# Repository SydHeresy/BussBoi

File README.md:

# BussBoi
 Eurorack IDC based bussing system.
 
 The frontpanel is not correct.

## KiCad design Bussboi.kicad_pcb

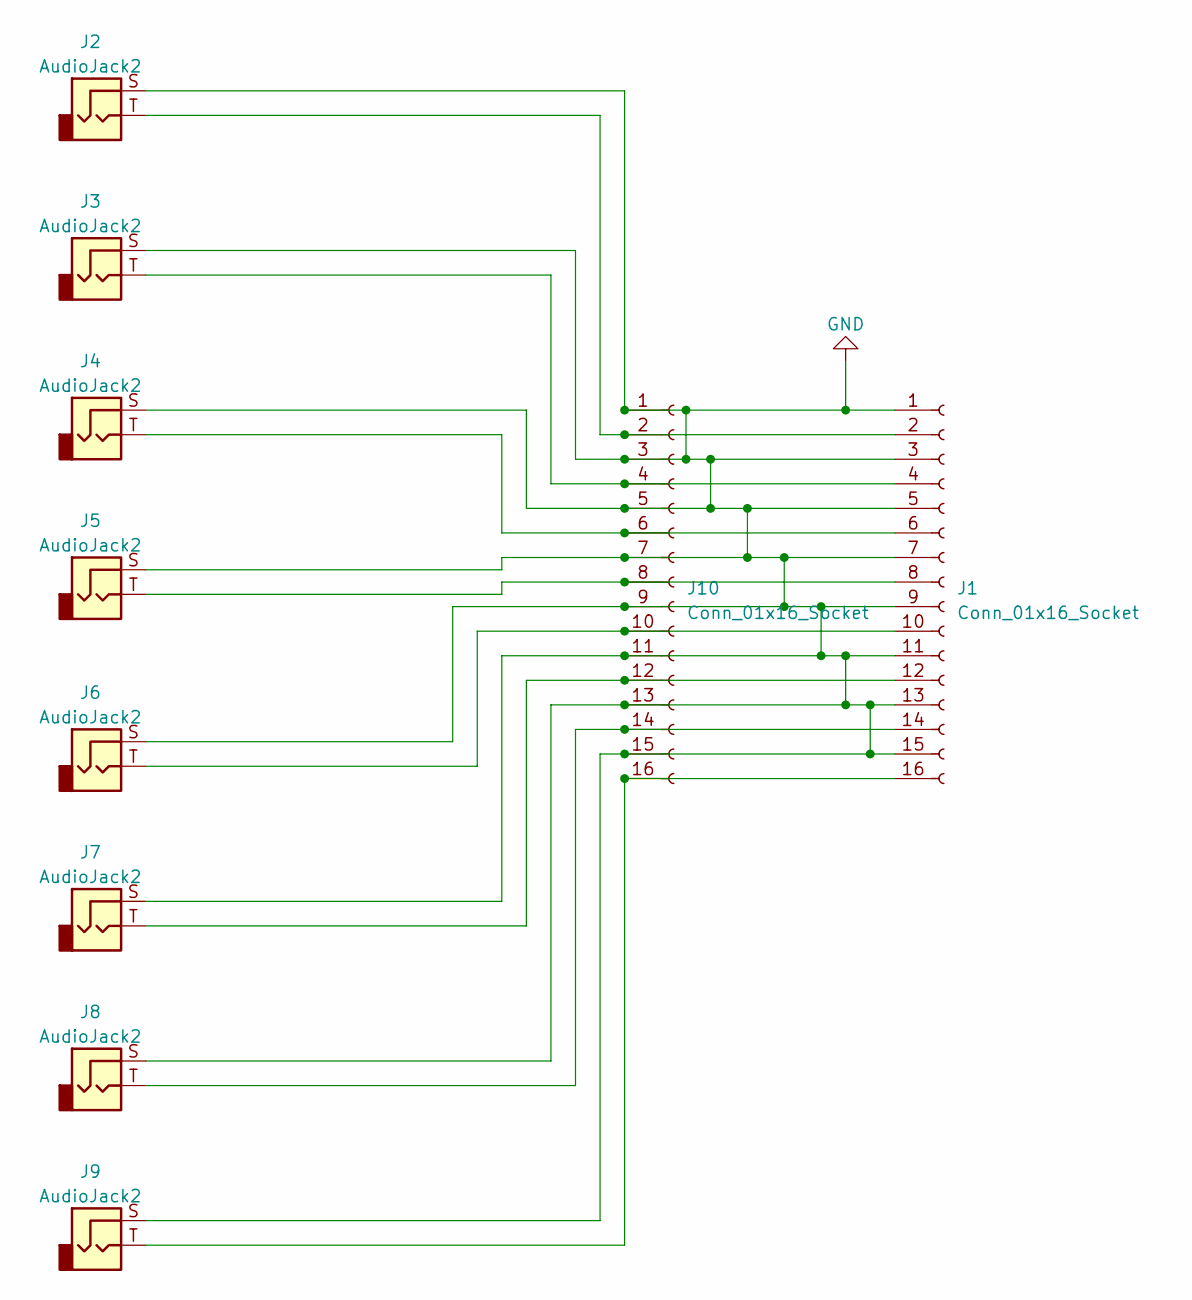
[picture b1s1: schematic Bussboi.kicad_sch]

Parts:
J1, J10: Conn_01x16_Socket; IDC-Header_2x08_P2.54mm_Vertical
J2, J3, J4, J5, J6, J7, J8, J9: AudioJack2; Jack_3.5mm_QingPu_WQP-PJ398SM_Vertical_CircularHoles

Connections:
GND: J1.1, J1.3, J1.5, J1.7, J1.9, J1.11, J1.13, J1.15, J2.S, J3.S, J4.S, J5.S, J6.S, J7.S, J8.S, J9.S, J10.1, J10.3, J10.5, J10.7, J10.9, J10.11, J10.13, J10.15
unnamed: J1.2, J2.T, J10.2
unnamed: J1.4, J3.T, J10.4
unnamed: J1.6, J4.T, J10.6
unnamed: J1.8, J5.T, J10.8
unnamed: J1.10, J6.T, J10.10
unnamed: J1.12, J7.T, J10.12
unnamed: J1.14, J8.T, J10.14
unnamed: J1.16, J9.T, J10.16

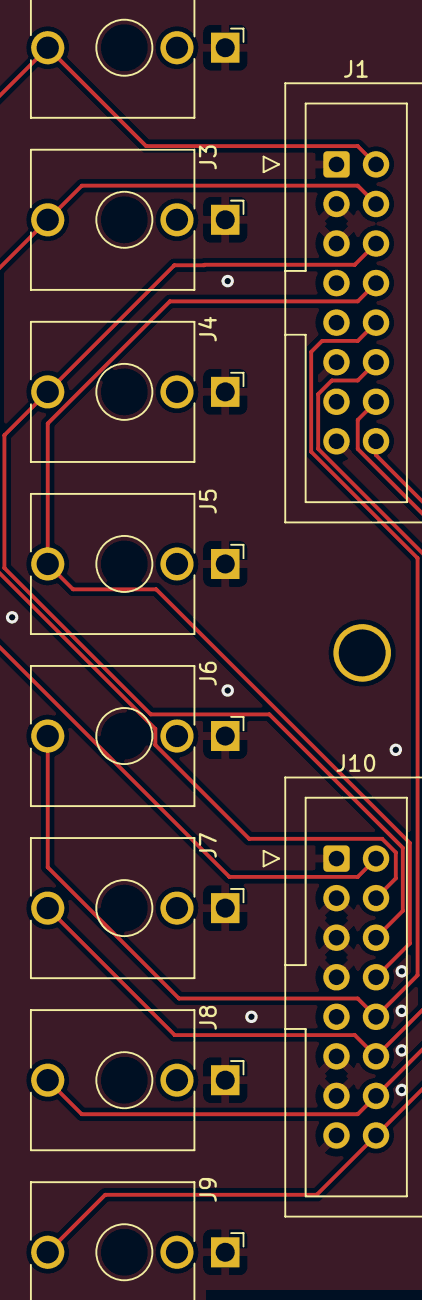
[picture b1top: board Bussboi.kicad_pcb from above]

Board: 2 copper layers, 10 parts (0 on the bottom side), 9 nets.

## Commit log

2023-04-02 updated PCB gerber files to have drill data.
